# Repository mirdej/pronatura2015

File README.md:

# pronatura2015
prairies fleuries

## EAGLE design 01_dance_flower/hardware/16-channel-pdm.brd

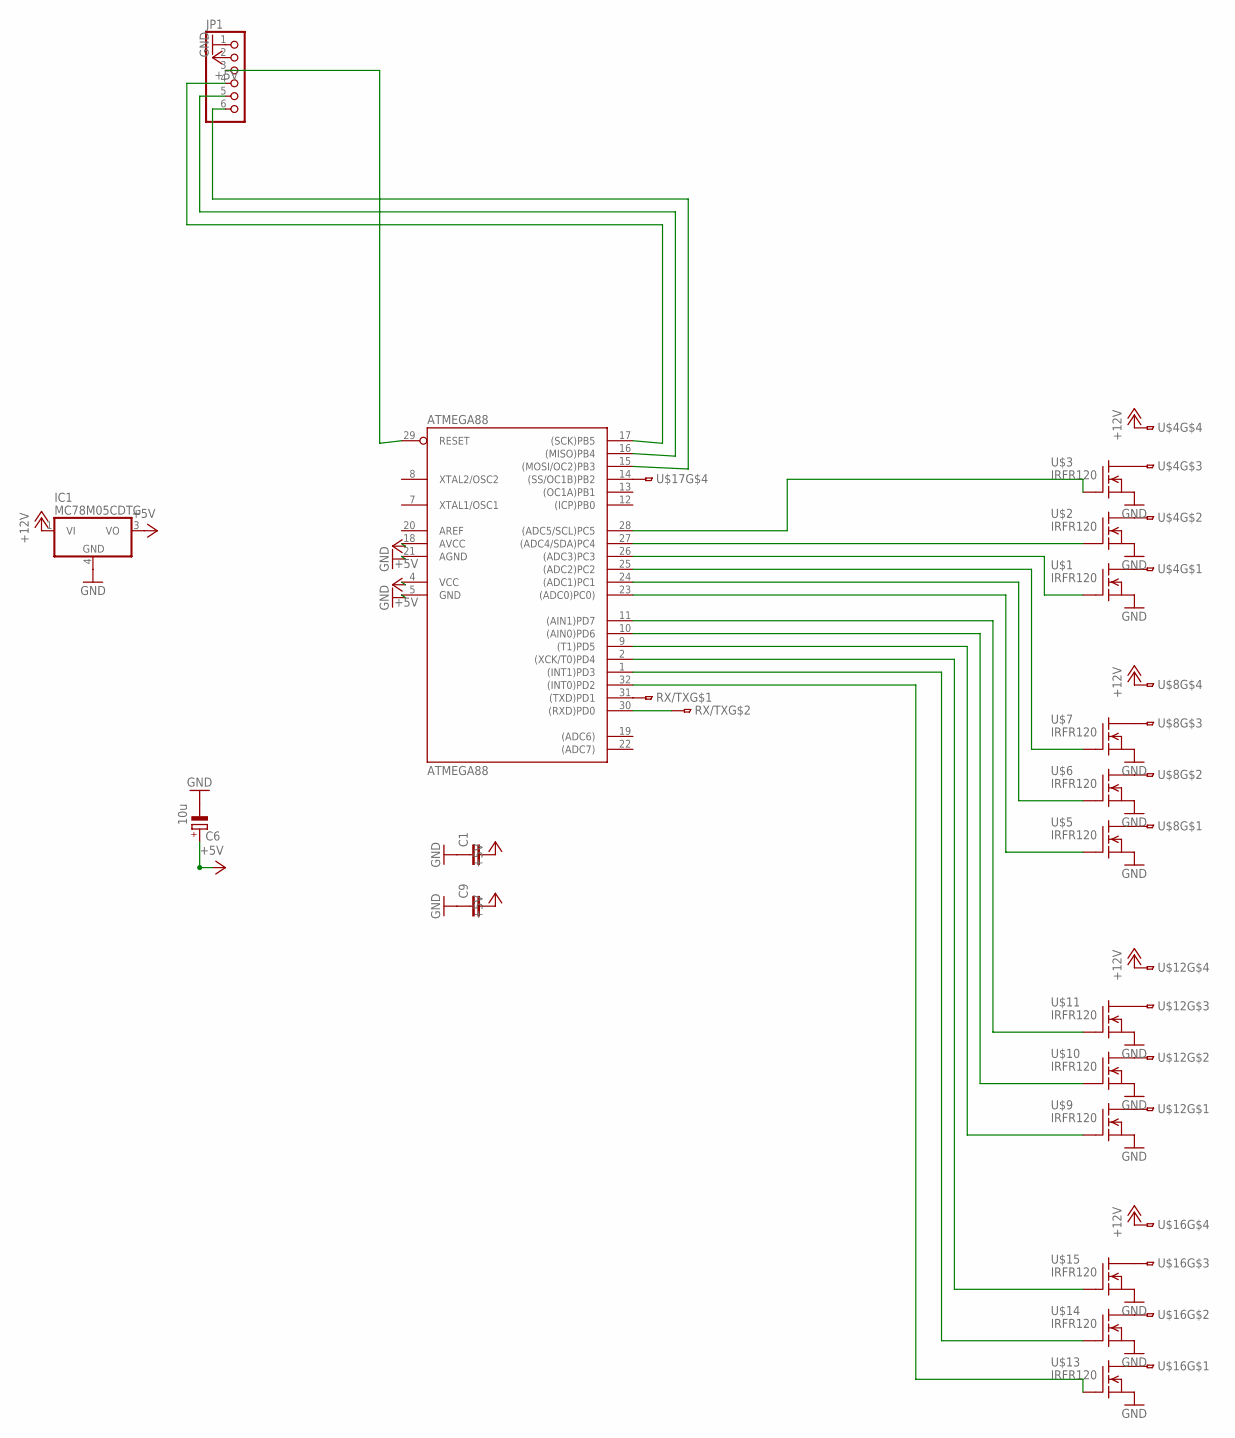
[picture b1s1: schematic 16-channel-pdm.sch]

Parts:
ATMEGA88: ATMEGA88; TQFP32-08
C1, C9: C-EUC0603; C0603
C6: 10u; CT3528
IC1: MC78M05CDTG; DPACK_3
JP1: PINHD-1X6; 1X06
RX/TX: 2PIN-SMD-2.54
U$1, U$2, U$3, U$5, U$6, U$7, U$9, U$10, U$11, U$13, U$14, U$15: IRFR120; DPAK
U$4, U$8, U$12, U$16, U$17: 4PIN-SMD; 4PIN-SMD-2.54

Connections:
+5V: ATMEGA88.4 (VCC), ATMEGA88.18 (AVCC), C1.2, C6.+, C9.2, IC1.3 (VO), JP1.2
+12V: IC1.1 (VI), U$4.4, U$8.4, U$12.4, U$16.4
AREF: ATMEGA88.20 (AREF)
GND: ATMEGA88.5 (GND), ATMEGA88.21 (AGND), C1.1, C6.-, C9.1, IC1.4 (GND), JP1.1, U$1.3 (S), U$2.3 (S), U$3.3 (S), U$5.3 (S), U$6.3 (S), U$7.3 (S), U$9.3 (S), U$10.3 (S), U$11.3 (S), U$13.3 (S), U$14.3 (S), U$15.3 (S)
unnamed: ATMEGA88.29 (RESET), JP1.3
unnamed: ATMEGA88.17 ((SCK)PB5), JP1.4
unnamed: ATMEGA88.16 ((MISO)PB4), JP1.5
unnamed: U$1.4 (D), U$4.1
unnamed: U$3.4 (D), U$4.3
unnamed: U$2.4 (D), U$4.2
unnamed: U$5.4 (D), U$8.1
unnamed: U$7.4 (D), U$8.3
unnamed: U$6.4 (D), U$8.2
unnamed: U$9.4 (D), U$12.1
unnamed: ATMEGA88.14 ((SS/OC1B)PB2), U$17.4
unnamed: U$11.4 (D), U$12.3
unnamed: U$10.4 (D), U$12.2
unnamed: U$13.4 (D), U$16.1
unnamed: U$15.4 (D), U$16.3
unnamed: U$14.4 (D), U$16.2
unnamed: ATMEGA88.28 ((ADC5/SCL)PC5), U$3.1 (G)
unnamed: ATMEGA88.27 ((ADC4/SDA)PC4), U$2.1 (G)
unnamed: ATMEGA88.15 ((MOSI/OC2)PB3), JP1.6
unnamed: ATMEGA88.26 ((ADC3)PC3), U$1.1 (G)
unnamed: ATMEGA88.25 ((ADC2)PC2), U$7.1 (G)
unnamed: ATMEGA88.24 ((ADC1)PC1), U$6.1 (G)
unnamed: ATMEGA88.23 ((ADC0)PC0)), U$5.1 (G)
unnamed: ATMEGA88.11 ((AIN1)PD7), U$11.1 (G)
unnamed: ATMEGA88.10 ((AIN0)PD6), U$10.1 (G)
unnamed: ATMEGA88.9 ((T1)PD5), U$9.1 (G)
unnamed: ATMEGA88.2 ((XCK/T0)PD4), U$15.1 (G)
unnamed: ATMEGA88.1 ((INT1)PD3), U$14.1 (G)
unnamed: ATMEGA88.32 ((INT0)PD2), U$13.1 (G)
unnamed: ATMEGA88.31 ((TXD)PD1), RX/TX.2
RX: ATMEGA88.30 ((RXD)PD0), RX/TX.3

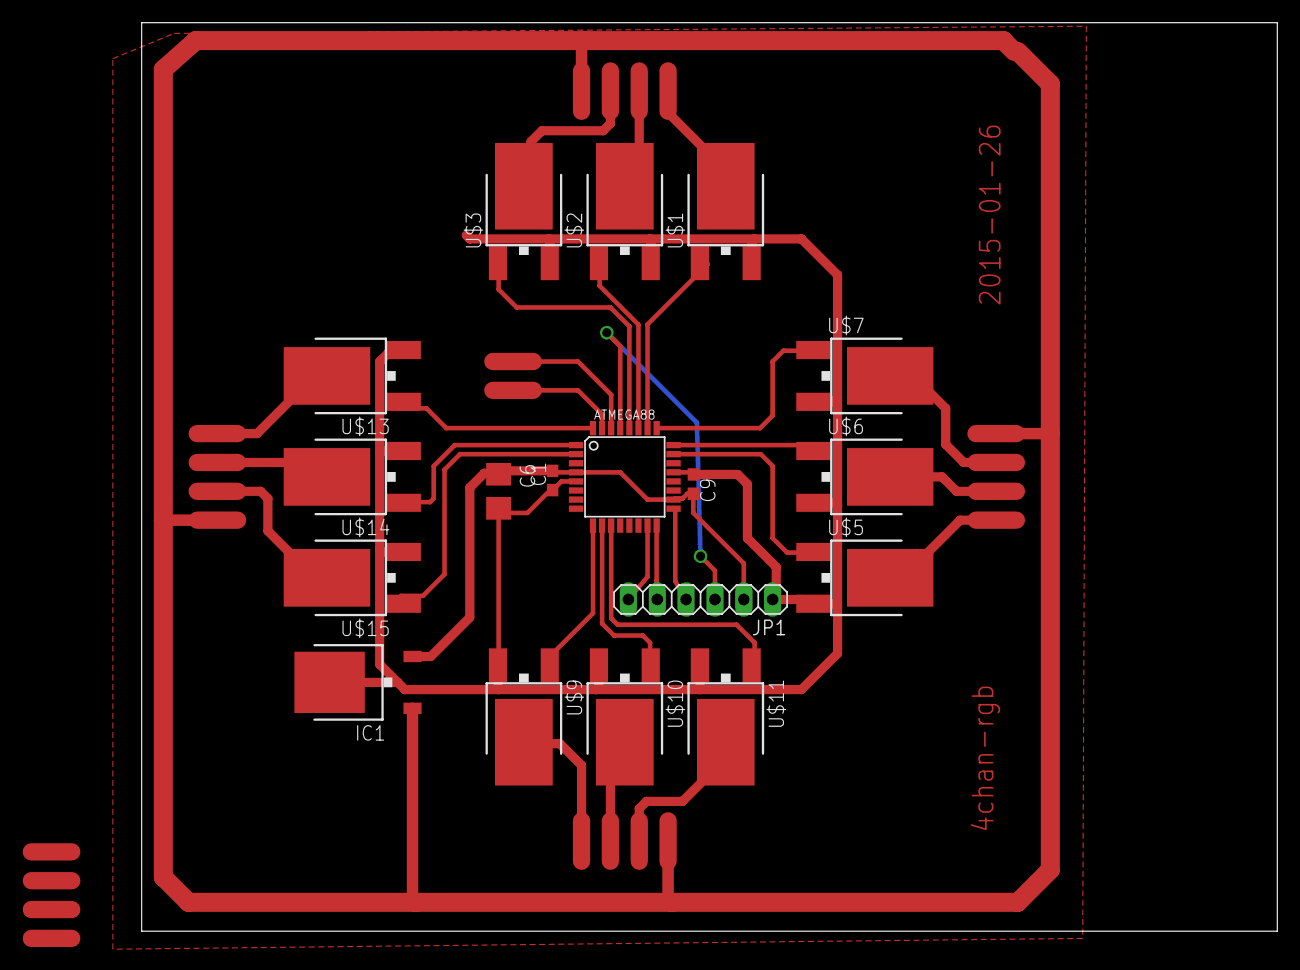
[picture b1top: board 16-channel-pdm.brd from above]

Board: 2 copper layers, 100.0 x 80.0 mm, 24 parts (0 on the bottom side), 34 nets.

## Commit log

2015-02-20 fix typo
2015-02-24 4 sensors
2015-02-24 new directory
2015-03-30 about to add maxmsp patches
2015-03-30 version as of vernissage
2015-03-30 trigger repetitif of same flower does not produce fail anymore
2015-06-21 made infochos a subpatcher so we can edit. changed fullscreen behavior when two screens
2015-06-21 controller with language choser buttons
2015-06-21 added language questions
2015-06-21 start screen with instriuctions
2015-06-21 language choser
2015-06-21 correct text problems, escape commas
